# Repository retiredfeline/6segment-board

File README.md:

# 6 segment 2 digit board

A more recent version is [available](https://github.com/retiredfeline/6segment-board-reloaded).

These are the Kicad design files for the [6 segment 2 digit board](https://hackaday.io/project/175397-6-segment-2-digit-led-board) project. Up to 3 boards can be cascaded for 6 digits.

This is a multiplexed design with 6 cathode segment drive lines (one colon line is unused), and up to 6 anode digit drive lines. The cathode drive lines are taken high to turn on the transistors, while the anode drive lines are taken low to turn on the transistors.

## Versioning

Release October 2020

## Notes

Most components are installed on the back side and the LEDs are installed on the front side.

The NPN transistors need a gain > 20 and the PNP transistors need a gain > 40. A bit more margin is recommended.

Note the the LED supply voltage will need to be higher than 4x the LED drop and the cathode current limiting resistor should be calculated accordingly. So 5V will not be sufficient and also a buffer stage will be needed for most MCUs. For example with a 12V supply and green (not emerald) LEDs, the voltage drop per LED is 2V. The transistor drops will be around 0.8V. That leaves 2.2V to be dropped across the resistor. A 220Ω resistor gives 10mA through the LED. For 4 digits multiplexed this is effectively 2.5mA. Modern LEDs are efficient enough to shine brightly at such currents. For dimming, use PWM.

When cascading only one board needs to be fully populated. The (up to 2) others only need the LEDs, the anode driver transistors, and its resistors. Also the PNP transistor base drive resistor leads are extended to fit the anode drive line connector holes for the digit select, starting with pin 1 for the leftmost digit.

The schematic shows cathode current limiting resistors in parallel with TM1810 constant current ICs. Only one needs to be installed. Only TM1810-30 was available to me and 30mA is too high a current for 3mm LEDs, even multiplexed so I stuck with the resistors.

## Authors

* **Ken Yap**

## License

See the [LICENSE](LICENSE.md) file for license rights and limitations (MIT).

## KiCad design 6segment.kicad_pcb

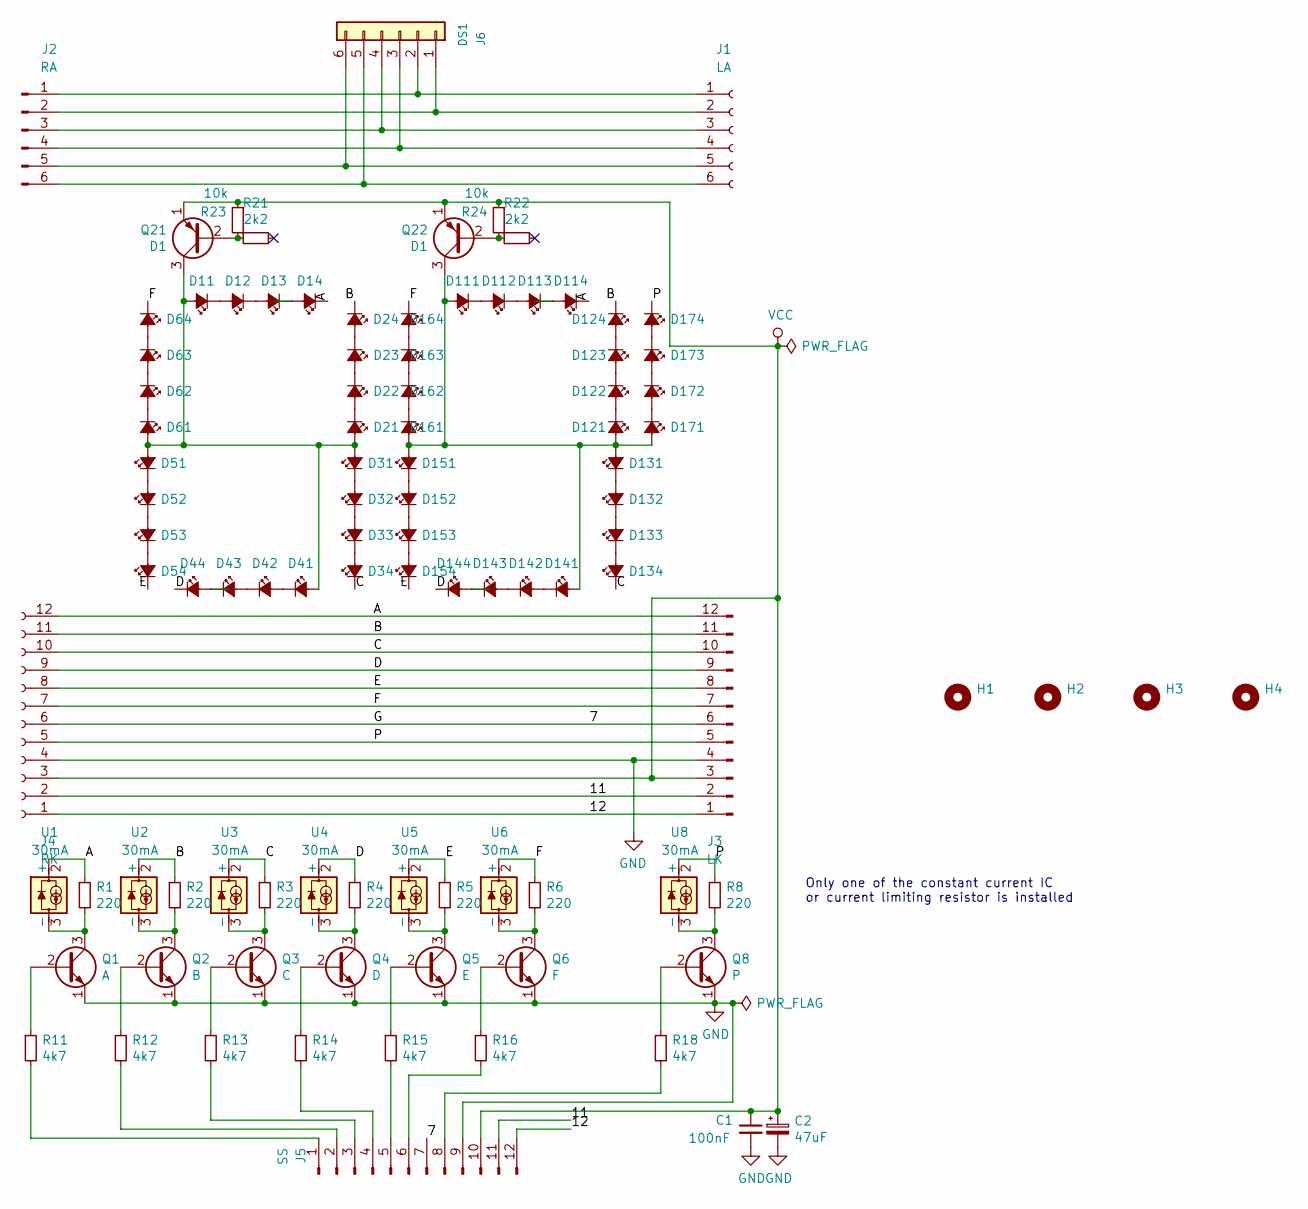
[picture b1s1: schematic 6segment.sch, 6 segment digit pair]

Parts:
C1: 100nF; C_Rect_L7.0mm_W2.0mm_P5.00mm
C2: 47uF; CP_Radial_D5.0mm_P2.50mm
D11, D12, D13, D14, D21, D22, D23, D24, D31, D32, D33, D34, D41, D42, D43, D44, D51, D52, D53, D54, D61, D62, D63, D64, D111, D112, D113, D114, D121, D122, D123, D124, D131, D132, D133, D134, D141, D142, D143, D144, D151, D152, D153, D154, D161, D162, D163, D164, D171, D172, D173, D174: 3mm; LED_D3.0mm
H1, H2, H3, H4: MountingHole; MountingHole_3.5mm
J1: LA; PinSocket_1x06_P2.54mm_Horizontal
J2: RA; PinHeader_1x06_P2.54mm_Horizontal
J3: LK; PinHeader_1x12_P2.54mm_Horizontal
J4: RK; PinSocket_1x12_P2.54mm_Horizontal
J5: SS; PinHeader_1x12_P2.54mm_Vertical
J6: DS1; 2X3
Q1: A; TO-92
Q2: B; TO-92
Q3: C; TO-92
Q4: D; TO-92
Q5: E; TO-92
Q6: F; TO-92
Q8: P; TO-92
Q21, Q22: D1; TO-92
R1, R2, R3, R4, R5, R6, R8: 220; R_Axial_DIN0309_L9.0mm_D3.2mm_P12.70mm_Horizontal
R11, R12, R13, R14, R15, R16, R18: 4k7; R_Axial_DIN0309_L9.0mm_D3.2mm_P12.70mm_Horizontal
R21, R22: 2k2; R_Axial_DIN0309_L9.0mm_D3.2mm_P12.70mm_Horizontal
R23, R24: 10k; R_Axial_DIN0309_L9.0mm_D3.2mm_P12.70mm_Horizontal
U1, U2, U3, U4, U5, U6, U8: 30mA; SOT-23

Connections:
/7: J3.6, J4.6, J5.7
/11: J3.2, J4.2, J5.11
/12: J3.1, J4.1, J5.12
/A: D14.1 (K), D114.1 (K), J3.12, J4.12, R1.1, U1.2 (+)
/B: D24.1 (K), D124.1 (K), J3.11, J4.11, R2.1, U2.2 (+)
/C: D34.1 (K), D134.1 (K), J3.10, J4.10, R3.1, U3.2 (+)
/D: D44.1 (K), D144.1 (K), J3.9, J4.9, R4.1, U4.2 (+)
/E: D54.1 (K), D154.1 (K), J3.8, J4.8, R5.1, U5.2 (+)
/F: D64.1 (K), D164.1 (K), J3.7, J4.7, R6.1, U6.2 (+)
/P: D174.1 (K), J3.5, J4.5, R8.1, U8.2 (+)
GND: C1.2, C2.2, J3.4, J4.4, J5.9, Q1.1 (E), Q2.1 (E), Q3.1 (E), Q4.1 (E), Q5.1 (E), Q6.1 (E), Q8.1 (E)
unnamed: D11.1 (K), D12.2 (A)
unnamed: D11.2 (A), D21.2 (A), D31.2 (A), D41.2 (A), D51.2 (A), D61.2 (A), Q21.3 (C)
unnamed: D12.1 (K), D13.2 (A)
unnamed: D13.1 (K), D14.2 (A)
unnamed: D21.1 (K), D22.2 (A)
unnamed: D22.1 (K), D23.2 (A)
unnamed: D23.1 (K), D24.2 (A)
unnamed: D31.1 (K), D32.2 (A)
unnamed: D32.1 (K), D33.2 (A)
unnamed: D33.1 (K), D34.2 (A)
unnamed: D41.1 (K), D42.2 (A)
unnamed: D42.1 (K), D43.2 (A)
unnamed: D43.1 (K), D44.2 (A)
unnamed: D51.1 (K), D52.2 (A)
unnamed: D52.1 (K), D53.2 (A)
unnamed: D53.1 (K), D54.2 (A)
unnamed: D61.1 (K), D62.2 (A)
unnamed: D62.1 (K), D63.2 (A)
unnamed: D63.1 (K), D64.2 (A)
unnamed: D111.1 (K), D112.2 (A)
unnamed: D111.2 (A), D121.2 (A), D131.2 (A), D141.2 (A), D151.2 (A), D161.2 (A), D171.2 (A), Q22.3 (C)
unnamed: D112.1 (K), D113.2 (A)
unnamed: D113.1 (K), D114.2 (A)
unnamed: D121.1 (K), D122.2 (A)
unnamed: D122.1 (K), D123.2 (A)
unnamed: D123.1 (K), D124.2 (A)
unnamed: D131.1 (K), D132.2 (A)
unnamed: D132.1 (K), D133.2 (A)
unnamed: D133.1 (K), D134.2 (A)
unnamed: D141.1 (K), D142.2 (A)
unnamed: D142.1 (K), D143.2 (A)
unnamed: D143.1 (K), D144.2 (A)
unnamed: D151.1 (K), D152.2 (A)
unnamed: D152.1 (K), D153.2 (A)
unnamed: D153.1 (K), D154.2 (A)
unnamed: D161.1 (K), D162.2 (A)
unnamed: D162.1 (K), D163.2 (A)
unnamed: D163.1 (K), D164.2 (A)
unnamed: D171.1 (K), D172.2 (A)
unnamed: D172.1 (K), D173.2 (A)
unnamed: D173.1 (K), D174.2 (A)
unnamed: J1.1, J2.1, J6.2
unnamed: J1.2, J2.2, J6.1
unnamed: J1.3, J2.3, J6.4
unnamed: J1.4, J2.4, J6.3
unnamed: J1.5, J2.5, J6.6
unnamed: J1.6, J2.6, J6.5
unnamed: J5.1, R11.2
unnamed: J5.2, R12.2
unnamed: J5.3, R13.2
unnamed: J5.4, R14.2
unnamed: J5.5, R15.2
unnamed: J5.6, R16.2
unnamed: J5.8, R18.2
unnamed: Q1.2 (B), R11.1
unnamed: Q1.3 (C), R1.2, U1.3 (-)
unnamed: Q2.2 (B), R12.1
unnamed: Q2.3 (C), R2.2, U2.3 (-)
unnamed: Q3.2 (B), R13.1
unnamed: Q3.3 (C), R3.2, U3.3 (-)
unnamed: Q4.2 (B), R14.1
unnamed: Q4.3 (C), R4.2, U4.3 (-)
unnamed: Q5.2 (B), R15.1
unnamed: Q5.3 (C), R5.2, U5.3 (-)
unnamed: Q6.2 (B), R16.1
unnamed: Q6.3 (C), R6.2, U6.3 (-)
unnamed: Q8.2 (B), R18.1
unnamed: Q8.3 (C), R8.2, U8.3 (-)
unnamed: Q21.2 (B), R21.1, R23.2
unnamed: Q22.2 (B), R22.1, R24.2
VCC: C1.1, C2.1, J3.3, J4.3, J5.10, Q21.1 (E), Q22.1 (E), R23.1, R24.1

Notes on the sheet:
Only one of the constant current IC or current limiting resistor is installed

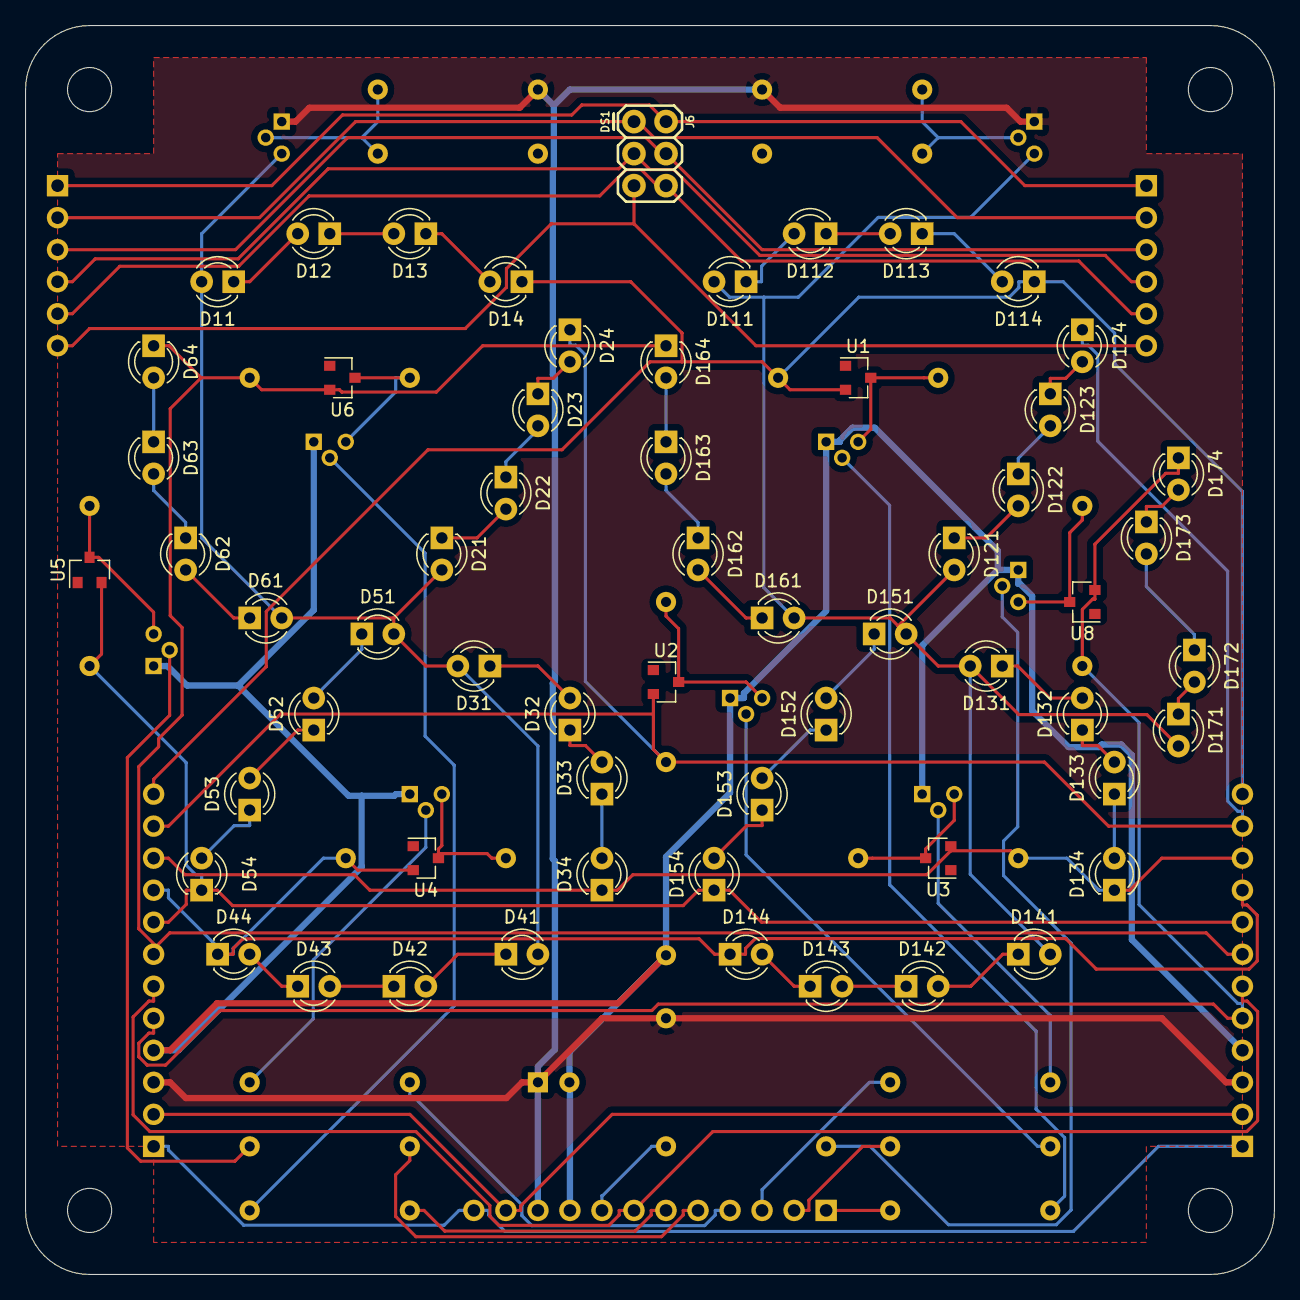
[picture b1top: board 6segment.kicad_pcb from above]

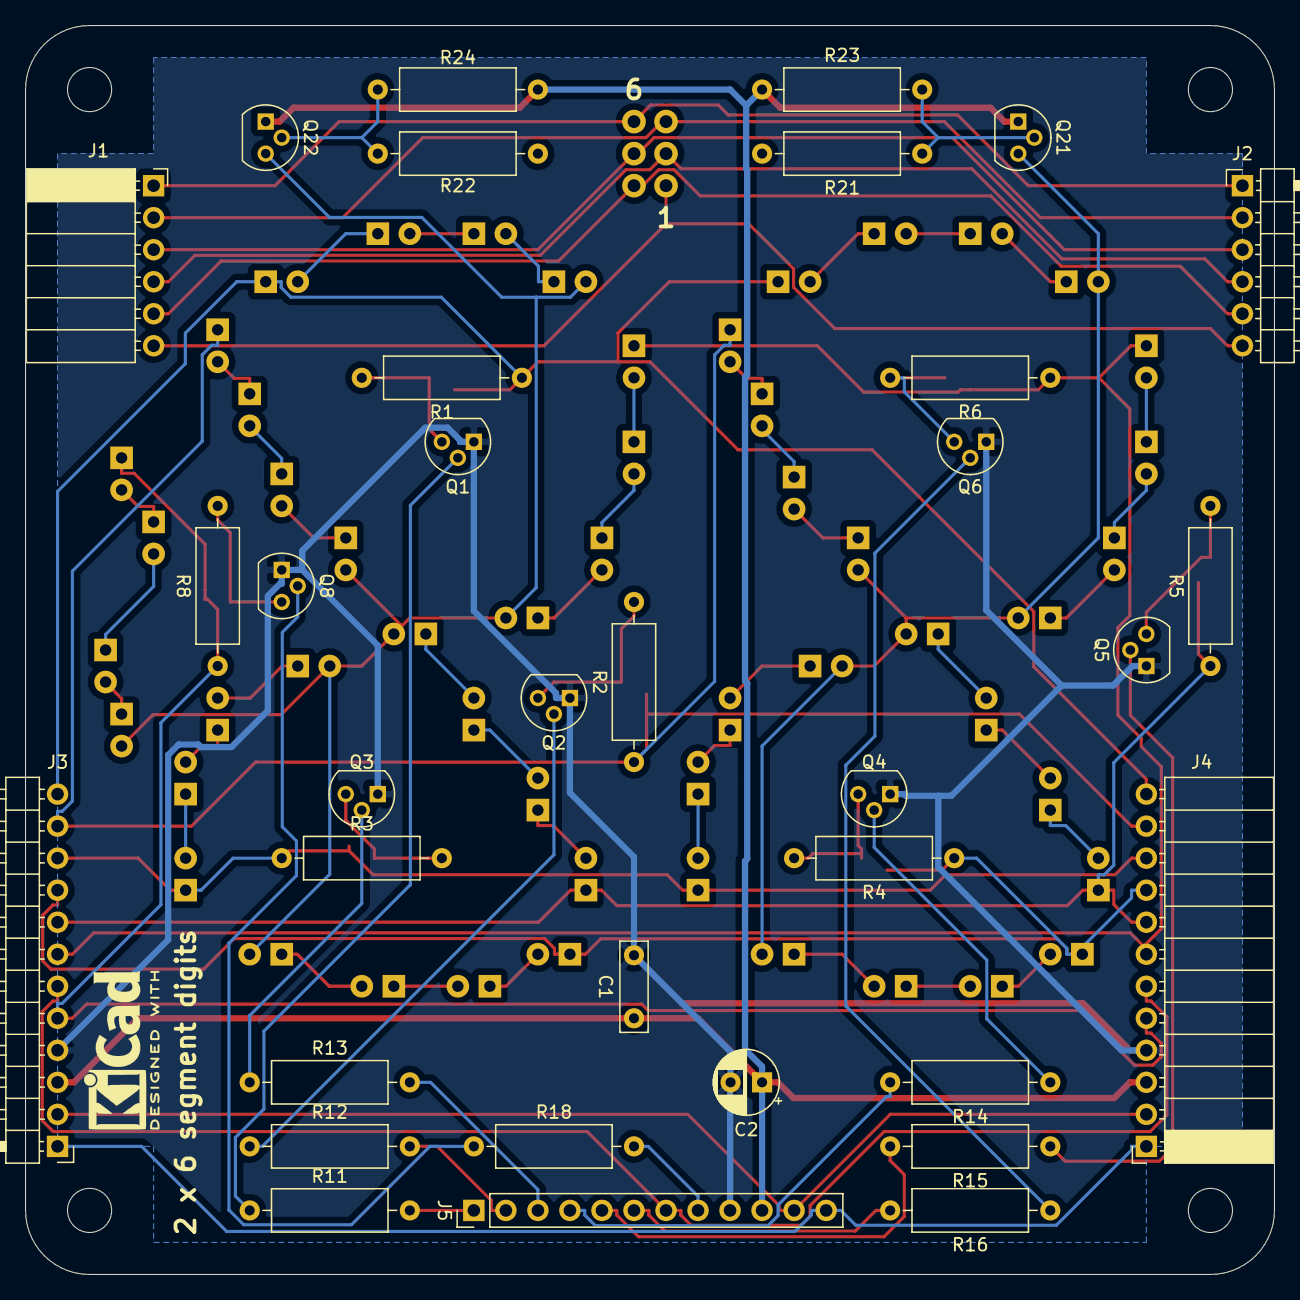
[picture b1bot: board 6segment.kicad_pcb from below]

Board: 2 copper layers, 99.1 x 99.1 mm, 98 parts (34 on the bottom side), 82 nets.

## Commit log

2020-10-15 Initial release
2022-02-17 Add link to newer version
